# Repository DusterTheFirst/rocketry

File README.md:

# Thrust Vector Controlled Model Rockets

This repository consists of the rockets that Zachary Kohnen has created. These rockets use active TVC based stabilization.
The models for each rocket can be found in the rockets directory, and the flight firmware for each project can be found in the firmware directory.
Below is a list of the rockets, basic information about them, and hyperlinks to their respective information.

You can access a development log published online at [rocketry.dusterthefirst.com](//rocketry.dusterthefirst.com) file.

# License
    Thrust Vector Controlled Model Rockets
    Copyright (C) 2020  Zachary Kohnen (DusterTheFirst)

    This program is free software: you can redistribute it and/or modify
    it under the terms of the GNU General Public License as published by
    the Free Software Foundation, either version 3 of the License, or
    (at your option) any later version.

    This program is distributed in the hope that it will be useful,
    but WITHOUT ANY WARRANTY; without even the implied warranty of
    MERCHANTABILITY or FITNESS FOR A PARTICULAR PURPOSE.  See the
    GNU General Public License for more details.

    You should have received a copy of the GNU General Public License
    along with this program.  If not, see <https://www.gnu.org/licenses/>.

<sub>All content in this repository was developed and maintained by [@DusterTheFirst (Zachary Kohnen)](https://github.com/dusterthefirst). Software and firmware is licensed under the [`GNU GPL 3.0 license`](./LICENSE.md) and CAD models and other artistic works are licensed under the [`CreativeCommons Attribution-NonCommercial-ShareAlike license`](http://creativecommons.org/licenses/by-nc-sa/4.0/)</sub>

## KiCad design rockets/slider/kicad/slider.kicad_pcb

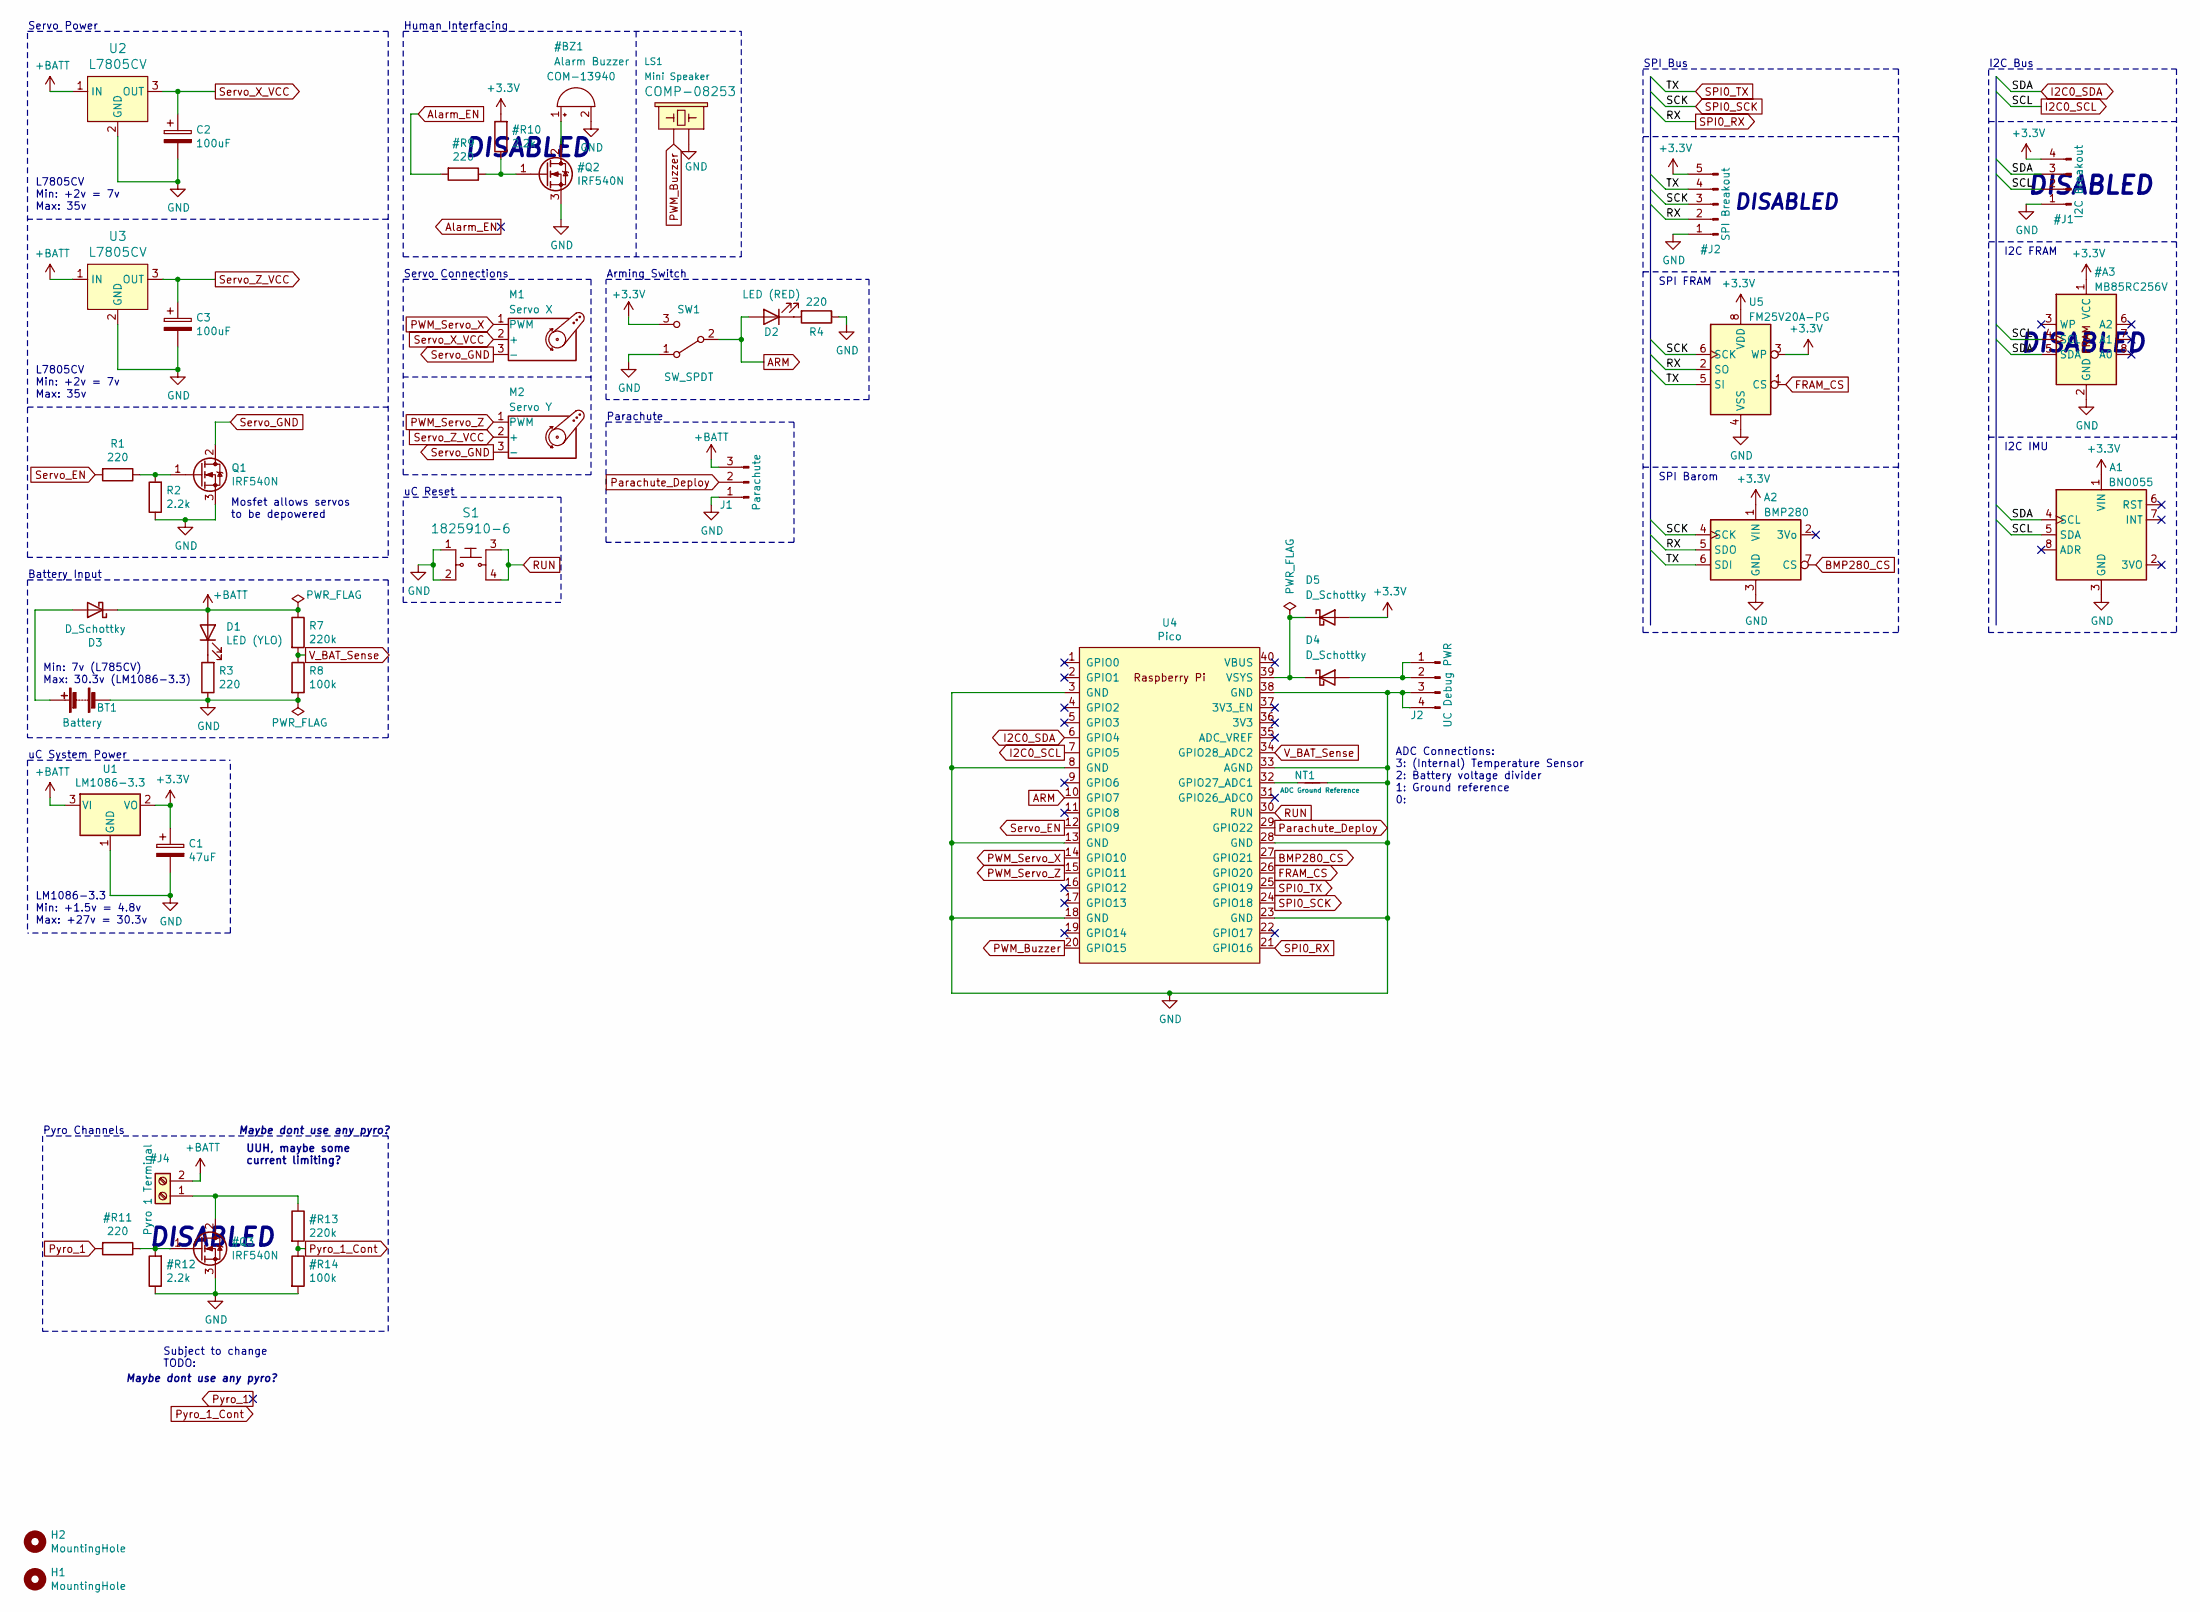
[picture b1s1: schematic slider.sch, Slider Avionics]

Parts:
A1: BNO055; Adafruit_BNO055
A2: BMP280; Adafruit_BMP280
BT1: Battery; TerminalBlock_Phoenix_PT-1,5-2-3.5-H_1x02_P3.50mm_Horizontal
C1: 47uF; CP_Radial_D5.0mm_P2.50mm
C2, C3: 100uF; CP_Radial_D6.3mm_P2.50mm
D1: LED (YLO); LED_D5.0mm
D2: LED (RED); LED_D5.0mm
D3, D4, D5: D_Schottky; D_DO-35_SOD27_P7.62mm_Horizontal
H1, H2: MountingHole; MountingHole_3mm
J1: Parachute; PinHeader_1x03_P2.54mm_Vertical
J2: UC Debug PWR; PinHeader_1x04_P2.54mm_Vertical
LS1: Mini Speaker; BUZZER-12MM
M1: Servo X; PinHeader_1x03_P2.54mm_Vertical
M2: Servo Y; PinHeader_1x03_P2.54mm_Vertical
NT1: ADC Ground Reference; NetTie-2_SMD_Pad0.5mm
Q1: IRF540N; TO-220-3_Vertical
R1, R3, R4: 220; R_Axial_DIN0207_L6.3mm_D2.5mm_P7.62mm_Horizontal
R2: 2.2k; R_Axial_DIN0207_L6.3mm_D2.5mm_P7.62mm_Horizontal
R7: 220k; R_Axial_DIN0207_L6.3mm_D2.5mm_P7.62mm_Horizontal
R8: 100k; R_Axial_DIN0207_L6.3mm_D2.5mm_P7.62mm_Horizontal
S1: 1825910-6; Switch_Tactile_THT_6x6mm; MPN 1825910-6; Digi-Key_PN 450-1650-ND
SW1: SW_SPDT; Switch_Toggle_ATE1D-2M3-10-Z
U1: LM1086-3.3; TO-220-3_Vertical
U2, U3: L7805CV; TO-220-3_Vertical; MPN L7805CV; Digi-Key_PN 497-1443-5-ND
U4: Pico; RPi_Pico_TH_Perfboard
U5: FM25V20A-PG; FM25V20A

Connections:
ARM: D2.2 (A), SW1.2 (B), U4.10 (GPIO7)
BMP280_CS: A2.7 (CS), U4.27 (GPIO21)
FRAM_CS: U4.26 (GPIO20), U5.1 (CS)
unnamed: BT1.1 (+), D3.2 (A)
unnamed: D1.1 (K), R3.2
unnamed: D2.1 (K), R4.2
unnamed: D4.1 (K), D5.1 (K), U4.39 (VSYS)
unnamed: D4.2 (A), J2.1, J2.2
unnamed: NT1.2, U4.32 (GPIO27_ADC1)
unnamed: Q1.1 (G), R1.1, R2.2
PWM_Buzzer: LS1.+ (1), U4.20 (GPIO15)
PWM_Servo_X: M1.1 (PWM), U4.14 (GPIO10)
PWM_Servo_Z: M2.1 (PWM), U4.15 (GPIO11)
Parachute_Deploy: J1.2, U4.29 (GPIO22)
RUN: S1.3, S1.4, U4.30 (RUN)
Servo_EN: R1.2, U4.12 (GPIO9)
Servo_GND: M1.3 (-), M2.3 (-), Q1.2 (D)
Servo_X_VCC: C2.1, M1.2 (+), U2.3 (OUT)
Servo_Z_VCC: C3.1, M2.2 (+), U3.3 (OUT)
V_BAT_Sense: R7.2, R8.1, U4.34 (GPIO28_ADC2)

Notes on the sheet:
Servo Power
uC System Power
Battery Input
Servo Connections
Human Interfacing
L7805CV Min: +2v = 7v Max: 35v
LM1086-3.3 Min: +1.5v = 4.8v Max: +27v = 30.3v
Min: 7v (L785CV) Max: 30.3v (LM1086-3.3)
uC Reset
Mosfet allows servos to be depowered
UUH, maybe some current limiting?
Pyro Channels
Subject to change TODO:
Arming Switch
Maybe dont use any pyro?
I2C Bus
SPI Bus
I2C FRAM
I2C IMU
SPI FRAM
SPI Barom
DISABLED
Parachute
ADC Connections: 3: (Internal) Temperature Sensor 2: Battery voltage divider 1: Ground reference 0:

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
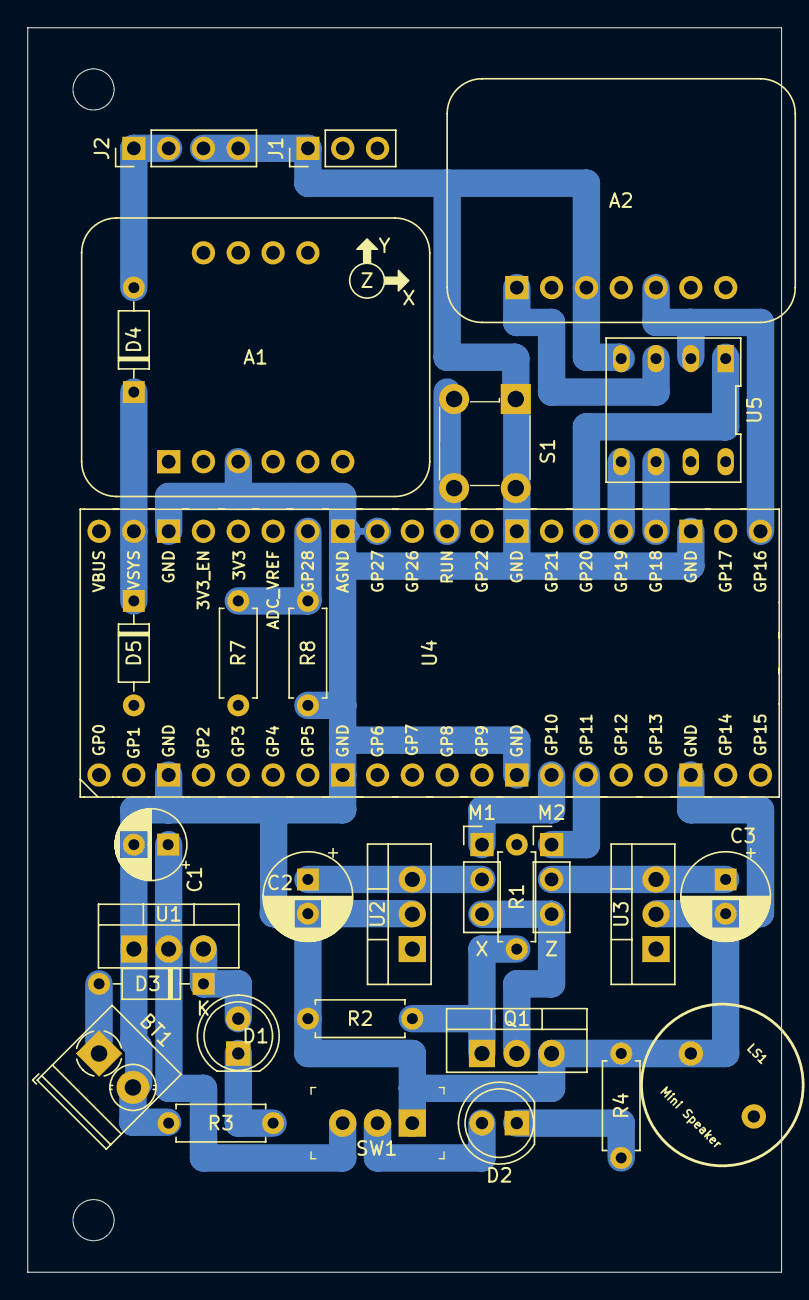
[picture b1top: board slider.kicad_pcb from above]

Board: 2 copper layers, 55.0 x 90.8 mm, 33 parts (1 on the bottom side), 28 nets.

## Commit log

2020-07-23 Initial File Structure
2020-07-23 Remove gcode from repo, since it is redundant
2020-07-23 rename stl folder to renders
2020-07-23 Rename cad models to rignt name
2020-07-25 Add parachute hoop to nose cone
2020-07-29 Better, lighter nose cone
2020-07-31 Stronger springs
2020-07-31 Fix export
2020-08-03 REorganise file structure
2020-08-04 realise that rust is too much work (at least for now)
2020-08-08 new nose cone mount
2020-08-13 New nose cone and parachute holder
    Two hold down strings will not work with the nichrome wire design due to them releasing at different times
2020-08-13 Addition of devlog and rename of firmware directory to avionics
2020-08-13 Add link to devlog in readme and fix links in devlog
2020-08-13 Fix footer link to profile
2020-08-13 Add github pages without exposing source code
2020-08-13 meta info
2020-08-13 remove meta
2020-08-13 change domain
2020-08-14 More hollow nosecone
2020-08-14 lowercase paths
2020-08-14 fix action
2020-08-14 change how gh pages works
2020-08-14 lowercase links
2020-08-14 what
2020-08-14 Change symbolic links to hard links
2020-08-14 Back to symlinks
2020-08-15 Plotter and basic comms with bmp-055
2020-08-15 enable all graphs with tiny time scale
2020-08-15 Less data points
2020-08-17 Setup simple rust interop
2020-08-17 More clean up and better poc
2020-08-18 simple interop
2020-08-18 Move more to rust
2020-08-18 move tones to rust
2020-08-19 some small changes
2020-08-21 Less unsafe
2020-08-22 rename interface to ui
2020-08-24 Beginnings of TVC mount
2020-08-24 Better design of TVC mount
2020-08-28 More TVC Gimbal Mount
2020-08-29 Better Middle TVC Mount
2020-08-31 Added drill holes to the middle gimbal
2020-08-31 Added more support under servo carrage and made the servo wires cutout better for 3d printing
2020-08-31 Exported new middle gimbal
2020-09-03 Thicker band around threaded inserts on gimbal
2020-09-04 Both servos aligned, just need to setup the connection mechanism ;)
2020-09-06 pure rust avionics
2020-09-08 mabye not rtic
2020-09-08 all rust is too new, going back to pio
2020-09-08 Move towards a more rust central approach
2020-09-09 more work towards level with old version
2020-09-09 decent enough rust only platform. moving to viper 0.2.0
2020-09-10 move to teensyuino and submodule
2020-09-10 change website theme
2020-09-10 dark theme
2020-09-10 revert theme
2020-09-12 upgrade the serial stack
2020-09-12 fix build script
2020-09-13 Documentation and servo pushrods
2020-09-13 move to stable rust and some move towards reading in sensors
2020-09-13 revert back to the c hybrid approach since the other one ran super slow for some reason
2020-09-18 Probbably v1 of gimbal done
2020-09-19 Finishing touches on TVC mount v1
2020-09-19 remove unused open rocket sim file
2020-11-01 New look for devlog
2020-11-02 Setup cdn
2020-11-02 TVC static fire test
2020-11-03 Fix videos
2020-11-03 Advertise github
2020-11-03 deploy: b26aa7ab97a135a0d54e742b71d4b6defa7dc3fa
2020-11-03 No force orphan for rendered branch
2020-11-03 Lots of devlogging
2020-11-03 deploy: 6a0581c7b28bcecedbceb67e670534b2f1c1c9f7
2021-01-28 oh yah
2021-01-28 deploy: 47cf73dbff4909dbb8601c8d4d09567671dbf674
2021-03-27 new work on pcb
2021-03-28 schematic
2021-03-28 More shematic
2021-03-28 Change schematic layout
2021-04-04 layouting
2021-04-12 assigned footprints
2021-04-13 Update mdbook-linkcheck
2021-04-13 Bruh, just cargo install it
2021-04-13 deploy: af08b000bdd1247698f3e6c2a43614688ca4eed0
2021-04-18 loads of pcb shiz
2021-05-27 busses
2021-05-27 deploy: 5b7f147d450ea07239b0ee580ce66044dfb8a59b
2021-05-28 remove backup files from version control
2021-05-29 Lots of work on busses and sensors
2021-05-31 Lots of 3d models for kicad and rethinking the pcb design
2021-06-19 Move custom library to https://github.com/DusterTheFirst/kicad-library
2021-06-19 Near v1 of board layout
2021-06-19 deploy: f617a62c9a7c7b926485a11277ef7631a520d374
2021-06-21 Routing and an additional pin header
2021-07-08 m4v => mp4 for better browser compat
2021-07-08 deploy: 97fca6f417c61f706d8c10d5dc18e63012417eca
